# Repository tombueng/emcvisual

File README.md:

# emcvisual

> Working title. The name lives only in `branding.config.json` and can be changed with a script,
> see [docs/RENAMING.md](docs/RENAMING.md).

**Try it in the browser:** https://tombueng.github.io/emcvisual/

You cannot see the electromagnetic fields of a circuit board. This tool computes them from a
board file and turns them into a **3D world you can look at and listen to**: where does it glow,
where does it hum, and what happens when the edge gets slower or the input capacitor moves closer
to the switching regulator?

It also checks about 30 known EMC layout mistakes, says what to do first, explains every finding
with its calculation and fix, and each time says why the statement could be wrong here. It is
built on a catalogue of mistakes with sources
([docs/research/EMC-MISTAKES-CATALOGUE.md](docs/research/EMC-MISTAKES-CATALOGUE.md)), a technical
review ([docs/review/TECHNICAL-REVIEW-2026-10.md](docs/review/TECHNICAL-REVIEW-2026-10.md)),
generated boards with each mistake as a test bench, and a comparison with a full-wave simulation.

Everything runs in the browser. The board file does not leave your computer. The user interface
speaks English and German.

## What it reads

| Format | From |
|---|---|
| KiCad `.kicad_pcb` (6 to 10) | KiCad |
| IPC-2581 `.xml` | Altium Designer, Cadence Allegro/OrCAD, Siemens PADS/Xpedition, Zuken, KiCad |
| ODB++ archive `.tgz` / `.zip` | the same tools and most CAM software |
| Eagle `.brd` (XML, Eagle 6 and later) | Autodesk Eagle, Fusion 360 Electronics |
| native files of Altium, Allegro, EasyEDA, CADSTAR, PADS, P-CAD, … | through KiCad's importers (`tools/convert/to_kicad.py`), then as `.kicad_pcb` |

Boards from IPC-2581 and ODB++ exports give the same board and the same results as the KiCad
original (checked on real boards). Eagle stores only the outlines of copper pours; the app pours
them itself, the way Eagle does. Details, export settings and limits:
[docs/IMPORT.md](docs/IMPORT.md).

## What it does

**Stage 1 (M0–M6), working:** quasi-static simulation of the magnetic near field (Biot–Savart with
image currents in the reference planes), and with it:

- import of KiCad, IPC-2581, ODB++ and Eagle boards; reference planes are detected, sources
  suggested from net names and parts
- sources: clock and data lines (also across series resistors), differential pairs, current
  loops of switching regulators (pads also picked in 3D), storage inductors
- the field as a glowing volume, isosurfaces, a slice plane, field lines of the selected source,
  ant view
- speech bubbles in 3D: the findings numbered at their place on the board (with their effect on
  the far field), sources with near field and distance to the limit, hotspots on request
- a virtual near-field probe with a spectrum analyser, a far-field estimate against selectable
  standards (CISPR 32, CISPR 11, CISPR 14-1, FCC Part 15) with an explanation of each standard
- sound: every source has a voice, loud where its field is strong
- diagnostics: interrupted return paths (also plane splits and narrow slots), reference changes
  at vias, missing stitching vias, unterminated lines with a resonance in the measured range,
  lines at the plane edge, signal layers without an adjacent plane, lines without a reference
  plane, hot loops and switch nodes of regulators, common mode with cables and crosstalk into
  cable lines (worst-case estimates), the regulators' switching current on the supply cable,
  filters bypassed by overlapping copper, filters and shields at connectors, ESD protection at
  USB/HDMI connectors, decoupling, crystals at the edge or a connector. All rules with threshold,
  origin and test board: [docs/RULES.md](docs/RULES.md). The findings are ordered by their share
  of the computed far field; the number on a bubble says what fixing only this spot changes in
  the model. Every finding has a priority (red, yellow, green), an explanation with the
  calculation, the fix, things to avoid, and the reasons why the statement could be wrong here
- real 3D part models: from your model folder or a GitHub repository (STEP, WRL, GLB, STL, found by
  file name), standard parts from KiCad's library, or from KiCad's GLB export
- scenarios as JSON, PNG and CSV export, an EMC report as HTML (printable as PDF)

Plan, acceptance criteria and notes: [docs/stage-1/PLAN.md](docs/stage-1/PLAN.md).

**Stage 2 (in progress):** return currents detour around slots in the plane and jump through the
nearest stitching via or capacitor at a layer change (the detours are shown in 3D); electric field
from line and node charges; stray field of open and shielded storage inductors. Details:
[docs/future/STAGE-2-PLANE-CURRENTS.md](docs/future/STAGE-2-PLANE-CURRENTS.md).

**Stage 3 (in progress):** full wave with openEMS. The app exports a job,
`tools/openems/run_job.py` computes it locally, and the result can be loaded next to the fast
model as a second field source: volume, probe, scan and far field. In the quasi-static range both
agree to about 1 dB; on a validation board the fast far field agrees with openEMS within 1 dB
between 30 and 350 MHz. Details: [tools/openems/README.md](tools/openems/README.md),
[docs/future/STAGE-3-FULL-WAVE.md](docs/future/STAGE-3-FULL-WAVE.md).

**Field check for CI:** the same calculation as a Node script. It reports near field, far-field
margin and layout findings per source and fails when a pull request makes something worse. The
script is at https://tombueng.github.io/emcvisual/cli/field-check.mjs, instructions in
[docs/CI-FIELD-CHECK.md](docs/CI-FIELD-CHECK.md).

**Stage 4 (in progress):** the "Measure" tab: a 3D printer moves a near-field probe over the
board, a receiver measures a spectrum at each point, and the result appears as a slice at the
measuring height and as a difference to the simulation. A virtual rig measures the simulation and
shows the whole chain without hardware; the drivers for OctoPrint, G-code over USB and the tinySA
are written but not yet tried on a device. Details:
[docs/future/STAGE-4-SCANNER.md](docs/future/STAGE-4-SCANNER.md).

What comes later (plane solver, phase and waves, hand probe, VR):
[docs/ROADMAP.md](docs/ROADMAP.md).

## Getting started

```bash
npm install
npm run dev
```

Then choose "Load demo board" in the browser, or drop your own board on the window
(`.kicad_pcb`, IPC-2581 `.xml`, ODB++ `.tgz`/`.zip` or Eagle `.brd`). In Chrome and Edge the app
follows the opened file: every save in the CAD program reloads the board, and sources and view
stay (badge "live" next to the file name). The step-by-step guide to every panel is
[docs/USER-GUIDE.md](docs/USER-GUIDE.md).

Real part models (right, under "Real 3D part models"): a KiCad board names only the path of each
part's model, such as `${KIPRJMOD}/3d/Relay.step` or
`${KICAD10_3DMODEL_DIR}/Package_SO.3dshapes/SOIC-8_3.9x4.9mm_P1.27mm.step`. The app looks for the
file by its name:

- in a **folder** on your computer ("Choose a folder with models …", with subfolders; the files
  stay in the browser),
- in a **GitHub repository** (`https://github.com/<owner>/<repo>` or a subfolder
  `…/tree/<branch>/<path>`),
- in the **project folder** of a board opened by link (`${KIPRJMOD}/…` sits next to the
  `.kicad_pcb`),
- in **KiCad's standard library** (from gitlab.com, STEP; can be switched off).

If a model exists several times, the same library folder wins, then STEP before GLB, WRL and STL.
STEP is triangulated in the browser with OpenCascade (WebAssembly, in the background), with the
colours from the file. Parts without a model found are listed.

Alternatively KiCad's own export: "File → Export → glTF/GLB" (without the board body) or
`kicad-cli pcb export glb --no-board-body --subst-models board.kicad_pcb`, then drop the `.glb`
on the window as well. The parts are matched by their reference; the GLB takes precedence over the
libraries. Boards from other CAD tools carry no model references; their parts are shown as boxes.

### Example boards to try

Public boards in every format the app reads, loaded straight from GitHub (also under "Examples …"
in the app, grouped by format):

| Board | Format | What is on it | Licence |
|---|---|---|---|
| Glasgow revC3 | KiCad | USB interface with FPGA, level shifters, 4 layers | 0BSD |
| HackRF One | KiCad | SDR 1 MHz to 6 GHz, USB, clocks, RF section | GPL-2.0 |
| Cynthion | KiCad | USB analyser, 6 layers, several USB PHYs | CERN-OHL-P-2.0 |
| Olimex ESP32-POE Rev M2 | KiCad | ESP32 with Ethernet (50 MHz clock) and PoE converter, split planes | Apache-2.0 |
| OtterCastAudio V2 | KiCad | audio streamer with SoC, Ethernet and USB | MIT |
| nRFMicro | KiCad | nRF52840 module for keyboards, 2 layers without a ground plane, own 3D models | Unlicense |
| I²C soil moisture sensor | KiCad | capacitive sensor with I²C, 4 layers, own 3D models | Apache-2.0 |
| Arduino Uno Rev3 | Eagle | the classic, 2 layers with ground pours | CC-BY-SA-2.5 |
| SparkFun ESP32 Thing | Eagle | ESP32 with LiPo charger, 2 layers | CC-BY-SA-4.0 |
| Adafruit ESP32-S3 TFT Feather | Eagle | ESP32-S3 with TFT and USB-C, 2 layers | CC-BY-SA-3.0 |
| Particle (Spark) Core | Eagle | STM32 with Wi-Fi, 4 layers with supply layers | CC-BY-SA-4.0 |
| BeagleBone Black | IPC-2581 | single-board computer with DDR3, 6 layers, from Cadence Allegro | CC-BY-SA-3.0 |
| IPC-2581 test case 10 | IPC-2581 | 18 layers, 576-ball BGA, negative planes | test data |
| Barreleye G2 Expander | ODB++ | PCIe expander of a POWER9 server, 10 layers, split power planes | OCPHL-P-1.0 |
| Barreleye G2 power distribution | ODB++ | 12 V and 48 V distribution, 6 layers | OCPHL-P-1.0 |
| Zaius LOM/VGA card | ODB++ | network and VGA card, 4 layers, negative ground planes | OCPHL-P-1.0 |

The boards belong to their projects and are under their licences; they are not in this
repository.

Boards can also be opened by link: `?demo` loads the demo, `?board=<URL>` a board file (any of the
formats above) from a server that allows cross-origin reads (e.g. `raw.githubusercontent.com`),
optionally with `&models=<URL>` for a GLB.
Example: [Glasgow revC3](https://tombueng.github.io/emcvisual/?board=https://raw.githubusercontent.com/GlasgowEmbedded/glasgow/HEAD/hardware/boards/glasgow/revC3/glasgow.kicad_pcb).

| Command | Purpose |
|---|---|
| `npm run dev` | development server |
| `npm test` | tests (physics against analytic solutions, parsers against pcbnew reference data, importers against KiCad's exports, the EMC test boards) |
| `npm run e2e` | Playwright tests in the browser (once before: `npx playwright install --only-shell chromium`) |
| `npm run check` | type check (TypeScript and Svelte) |
| `npm run build` | static site into `dist/`, and the field check into `dist/cli/` |
| `npm run field-check -- board.kicad_pcb --scenario s.json` | field check without a browser, e.g. in CI; also takes IPC-2581, ODB++ and Eagle files ([docs/CI-FIELD-CHECK.md](docs/CI-FIELD-CHECK.md)) |
| `npm run demo-board` | regenerate the demo board with KiCad (pcbnew Python) |
| `npm run check:codename` | checks that the working title appears only where it may |

## What the simulation can and cannot do

It shows **where** current loops create magnetic fields and how changes to loop area, return path
and edges affect those fields, and it finds the known layout mistakes (checked on generated boards
with each mistake, `tools/emc-cases`). It does **not** predict whether a device passes an EMC
test: tests mostly fail on common-mode currents on cables, which the app estimates only roughly
for the worst case; there are no resonances and no enclosure. Every explanation says why its
number could be wrong here. Assumptions and limits are in
[docs/stage-1/PHYSICS.md](docs/stage-1/PHYSICS.md), the known kinds of mistakes in
[docs/research/EMC-MISTAKES-CATALOGUE.md](docs/research/EMC-MISTAKES-CATALOGUE.md), the
technical review in [docs/review/TECHNICAL-REVIEW-2026-10.md](docs/review/TECHNICAL-REVIEW-2026-10.md).

## Documentation

- [docs/USER-GUIDE.md](docs/USER-GUIDE.md): how to use the app, panel by panel, with a FAQ and a
  glossary
- [docs/IMPORT.md](docs/IMPORT.md): boards from other CAD tools (IPC-2581, ODB++, Eagle)
- [docs/RULES.md](docs/RULES.md): every finding with threshold, origin, confidence and test board
- [docs/research/EMC-MISTAKES-CATALOGUE.md](docs/research/EMC-MISTAKES-CATALOGUE.md): 40 layout
  mistakes with mechanism, lab symptom, detection rule, fix and sources
- [docs/stage-1/PHYSICS.md](docs/stage-1/PHYSICS.md): model, formulas, validity, literature,
  comparison with full wave
- [docs/stage-1/ARCHITECTURE.md](docs/stage-1/ARCHITECTURE.md): structure of the app
- [docs/stage-1/PLAN.md](docs/stage-1/PLAN.md): goals, milestones, acceptance criteria
- [docs/review/TECHNICAL-REVIEW-2026-10.md](docs/review/TECHNICAL-REVIEW-2026-10.md): review of the
  physical and normative statements
- [docs/DECISIONS.md](docs/DECISIONS.md): decisions with their reasons
- [docs/ROADMAP.md](docs/ROADMAP.md): stages and dependencies
- [docs/future/](docs/future/): stages 2 to 5 and cross-cutting topics
- [docs/CI-FIELD-CHECK.md](docs/CI-FIELD-CHECK.md): the field check in CI
- [docs/AI-PARTS-MANUAL.md](docs/AI-PARTS-MANUAL.md): how an AI agent can fill in the source
  parameters of a board

## Licence

[0BSD](LICENSE) (Zero-Clause BSD): anyone may use, change and share the code for any purpose,
also commercially, without attribution. openEMS (stage 3) is under GPL-3.0 and installed
separately; it is not part of this repository. To read STEP models the app loads
[occt-import-js](https://github.com/kovacsv/occt-import-js) (OpenCascade as WebAssembly,
LGPL-2.1) unchanged as its own worker with its own `.wasm` file; its licence applies to it.

---

<!-- disclaimer-notice:v1 -->
## ⚖️ Haftungsausschluss / Disclaimer

> **Deutsch**
>
> Diese Software bzw. dieses Hardware-Design wird **unentgeltlich** und **„wie besehen" (as is)**
> bereitgestellt — ohne jede ausdrückliche oder stillschweigende Gewährleistung. Insbesondere
> werden **keine Eigenschaften zugesichert** und **keine Garantie** für Mängelfreiheit, Richtigkeit,
> Vollständigkeit, Aktualität, Verfügbarkeit, handelsübliche Qualität, Eignung für einen bestimmten
> Zweck oder die Nichtverletzung von Rechten Dritter übernommen. Die Nutzung erfolgt **auf eigenes
> Risiko**; die Eignung für den konkreten Einsatz ist vor der Verwendung eigenverantwortlich zu prüfen
> — das gilt besonders beim Ansteuern realer Hardware sowie in sicherheits- oder betriebskritischen
> Umgebungen.
>
> Eine Haftung des Autors für Schäden gleich welcher Art, die aus der Nutzung oder Nichtnutzbarkeit
> entstehen, ist — soweit gesetzlich zulässig — ausgeschlossen.
>
> **Unberührt** bleibt die zwingende gesetzliche Haftung: für Vorsatz und grobe Fahrlässigkeit, für
> die schuldhafte Verletzung von Leben, Körper oder Gesundheit, nach dem Produkthaftungsgesetz sowie
> aus einer ausdrücklich übernommenen Garantie. Ergänzend gelten die Haftungserleichterungen der
> §§ 521, 523, 524 BGB für die unentgeltliche Überlassung.
>
> Dies ist Freizeit-/Open-Source-Arbeit; es besteht **kein Anspruch auf Support, Wartung oder
> Weiterentwicklung**, und das Projekt kann jederzeit geändert oder eingestellt werden. Genannte
> Produkt- und Markennamen gehören ihren jeweiligen Inhabern; es besteht **keine Verbindung zu,
> Billigung durch oder Partnerschaft mit** diesen Unternehmen.

> **English**
>
> This software / hardware design is provided **free of charge** and **"as is"**, without warranty of
> any kind, express or implied. In particular, **no warranties and no guaranteed characteristics** are
> given — including, without limitation, merchantability, fitness for a particular purpose, correctness,
> accuracy, completeness, availability, or non-infringement. **Use is at your own risk**; you are
> responsible for verifying suitability for your intended use before relying on it, especially when
> driving real hardware or in safety- or mission-critical environments.
>
> To the maximum extent permitted by applicable law, the author shall **not be liable** for any damages
> whatsoever arising from the use of, or inability to use, this work.
>
> Mandatory statutory liability remains **unaffected** (under German law: liability for intent and gross
> negligence, for culpable injury to life, body or health, under the Product Liability Act, and from any
> expressly given guarantee).
>
> This is a hobby / open-source project with **no obligation of support, maintenance or further
> development**, and it may be changed or discontinued at any time. All product and brand names are the
> property of their respective owners; this project is **not affiliated with, endorsed, or sponsored by**
> them.

The applicable open-source license (see [`LICENSE`](./LICENSE)) governs use, reproduction and
distribution. In case of any conflict between this notice and the `LICENSE`, the `LICENSE` prevails.

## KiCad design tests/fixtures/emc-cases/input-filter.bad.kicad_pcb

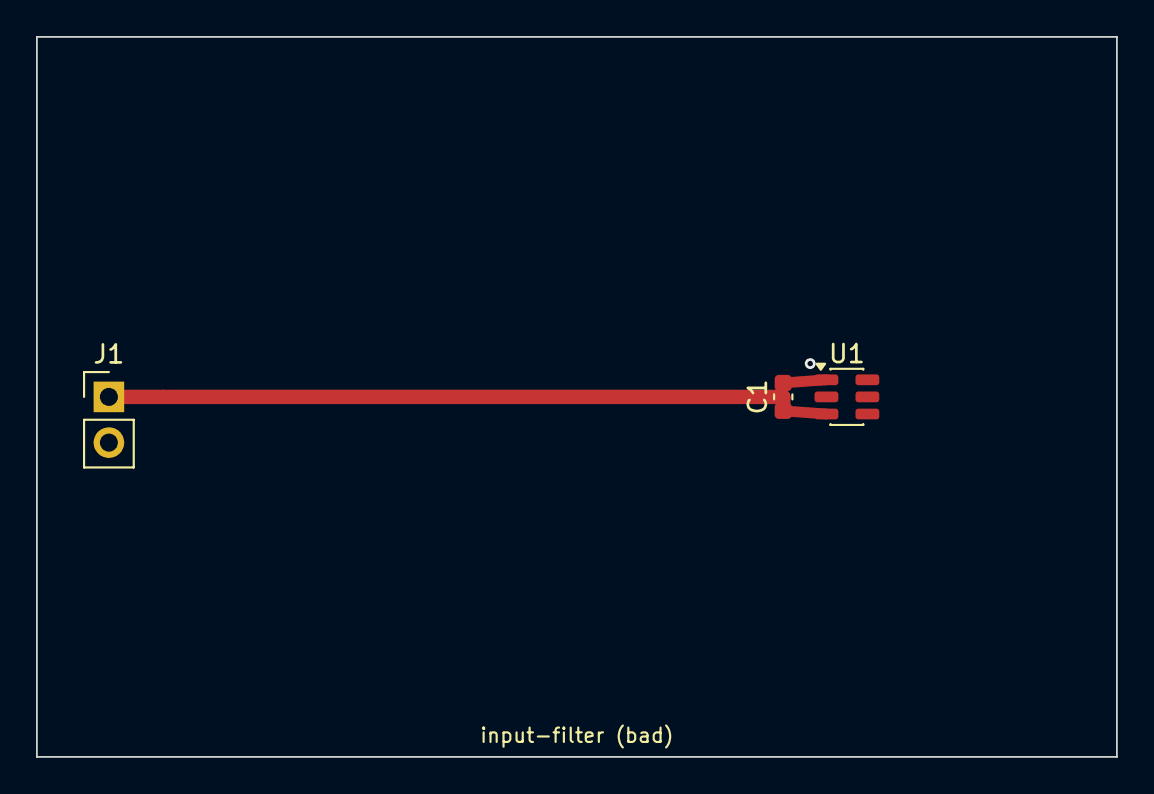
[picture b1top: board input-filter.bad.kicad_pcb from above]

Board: 2 copper layers, 60.0 x 40.0 mm, 3 parts (0 on the bottom side), 2 nets.

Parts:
C1: 10uF; C_0603_1608Metric
J1: DC 12V; PinHeader_1x02_P2.54mm_Vertical
U1: TPS562201; SOT-23-6

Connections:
+12V_IN: C1.1, J1.1, U1.3
GND: C1.2, J1.2, U1.1

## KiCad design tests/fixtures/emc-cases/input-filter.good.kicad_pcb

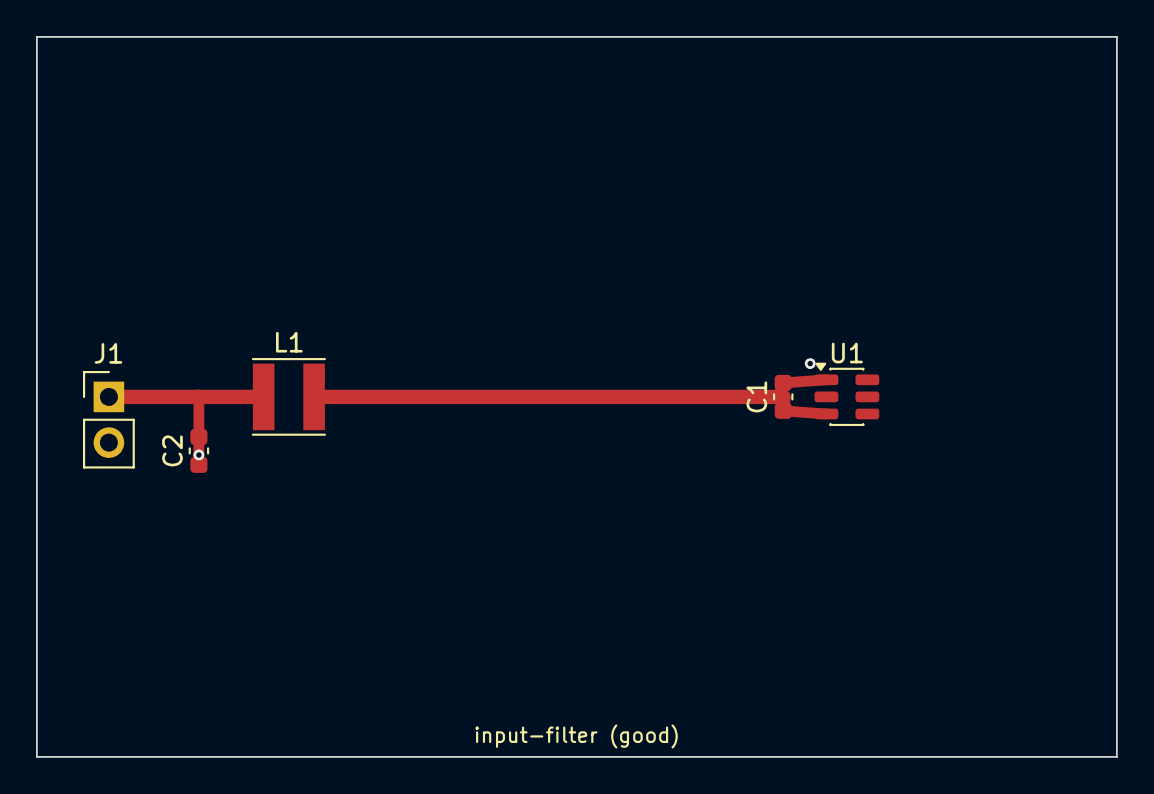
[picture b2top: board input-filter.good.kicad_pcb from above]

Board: 2 copper layers, 60.0 x 40.0 mm, 5 parts (0 on the bottom side), 3 nets.

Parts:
C1: 10uF; C_0603_1608Metric
C2: 4.7uF; C_0603_1608Metric
J1: DC 12V; PinHeader_1x02_P2.54mm_Vertical
L1: 10uH; L_Taiyo-Yuden_NR-40xx
U1: TPS562201; SOT-23-6

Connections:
+12V_IN: C2.1, J1.1, L1.1
GND: C1.2, C2.2, J1.2, U1.1
VIN: C1.1, L1.2, U1.3

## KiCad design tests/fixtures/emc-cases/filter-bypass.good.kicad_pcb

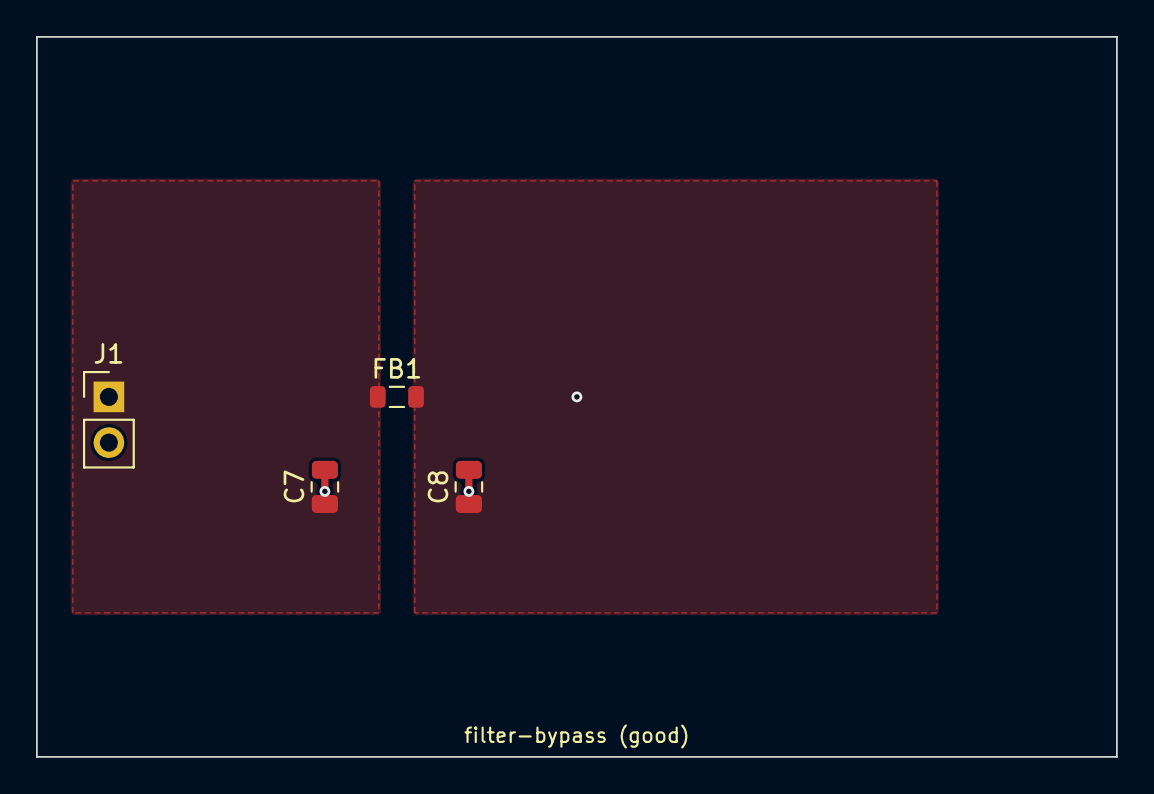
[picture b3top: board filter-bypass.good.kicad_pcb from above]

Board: 4 copper layers, 60.0 x 40.0 mm, 4 parts (0 on the bottom side), 3 nets.

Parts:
C7: 100nF; C_0805_2012Metric
C8: 1uF; C_0805_2012Metric
FB1: 600R@100MHz; L_0805_2012Metric
J1: DC; PinHeader_1x02_P2.54mm_Vertical

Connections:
+12V_F: C8.1, FB1.2
+12V_IN: C7.1, FB1.1, J1.1
GND: C7.2, C8.2, J1.2

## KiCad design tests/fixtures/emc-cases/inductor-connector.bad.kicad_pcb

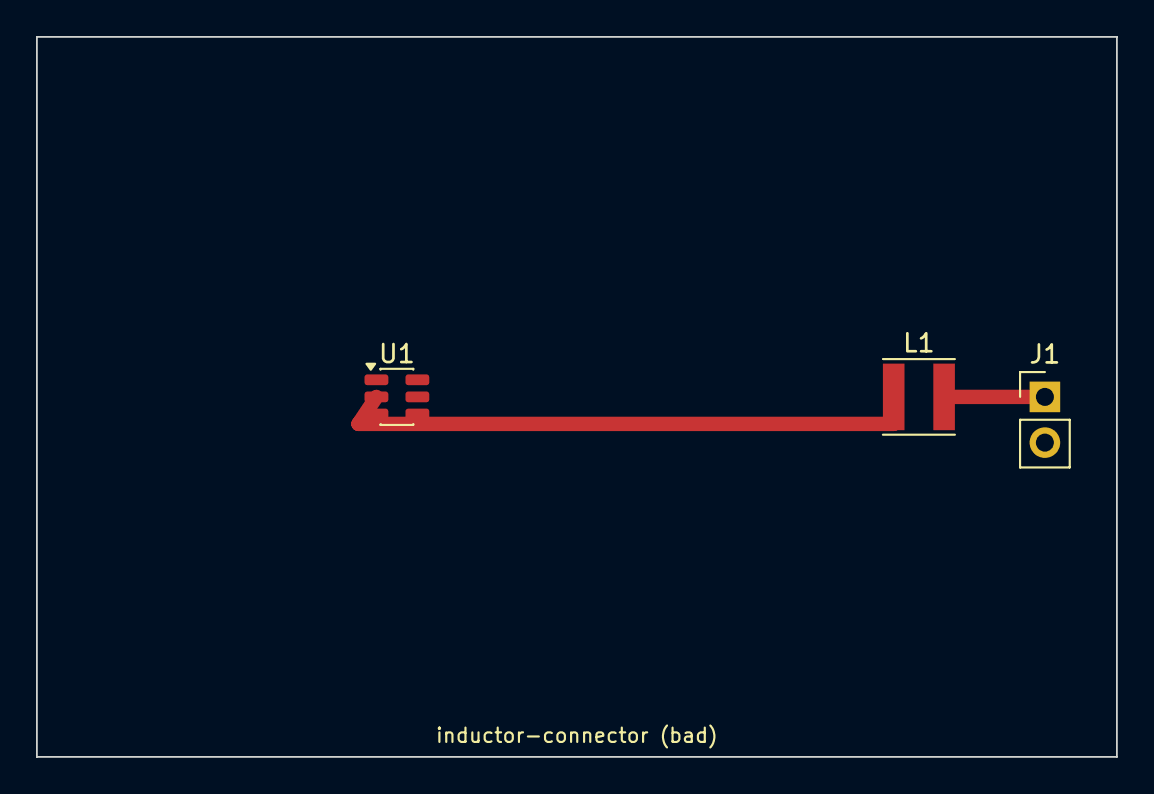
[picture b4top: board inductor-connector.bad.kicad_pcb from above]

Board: 4 copper layers, 60.0 x 40.0 mm, 3 parts (0 on the bottom side), 3 nets.

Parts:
J1: OUT; PinHeader_1x02_P2.54mm_Vertical
L1: 4.7uH; L_Taiyo-Yuden_NR-40xx
U1: TPS562201; SOT-23-6

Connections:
GND: J1.2, U1.1
SW: L1.1, U1.2
VOUT: J1.1, L1.2
